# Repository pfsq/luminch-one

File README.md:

Luminch One
===========

Luminch One is an interactive lamp controlled by the movements of your hand.
Wave your hand over it to turn it on or off, or move your hand up or down
above it to change its brightness. Inside the lamp, an Arduino hooked to an
infrared distance sensor tracks your hand and sets the state and the
brightness of the LED lamp.

Copyright 2012 by [Francisco Castro](http://fran.cc)

EAGLE files, copyleft (ɔ) 2013 by [Pablo Fernández](http://theansweris27.wordpress.com)

[More info...](http://fran.cc/post/15139791161/luminch-one)

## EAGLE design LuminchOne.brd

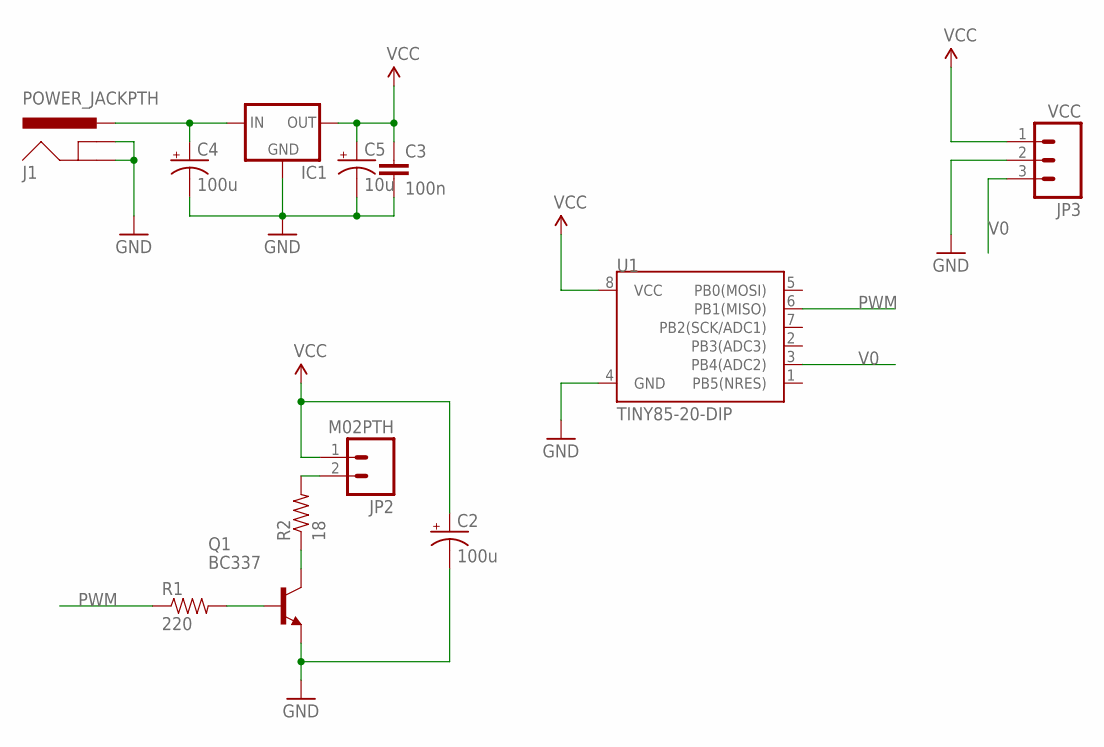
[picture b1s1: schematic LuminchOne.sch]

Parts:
C2, C4: 100u; CPOL-RADIAL-100UF-25V
C3: 100n; CAP-PTH-SMALL
C5: 10u; CPOL-RADIAL-10UF-25V
IC1: V_REG_78XX-TO-220; TO-220-ALT
J1: POWER_JACKPTH; POWER_JACK_PTH
JP2: M02PTH; 1X02
JP3: VCC; 1X03
Q1: BC337; TO92
R1: 220; AXIAL-0.4
R2: 18; AXIAL-0.6
U1: TINY85-20-DIP; DIP08

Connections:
GND: C2.2 (-), C3.2, C4.2 (-), C5.2 (-), IC1.GND, J1.GND, J1.GNDBREAK, JP3.2, Q1.1 (E), U1.4 (GND)
unnamed: Q1.2 (B), R1.P$2 (2)
unnamed: JP2.2, R2.P$2 (2)
unnamed: C4.1 (+), IC1.IN, J1.PWR
unnamed: Q1.3 (C), R2.P$1 (1)
PWM: R1.P$1 (1), U1.6 (PB1(MISO))
V0: JP3.3, U1.3 (PB4(ADC2))
VCC: C2.1 (+), C3.1, C5.1 (+), IC1.OUT, JP2.1, JP3.1, U1.8 (VCC)

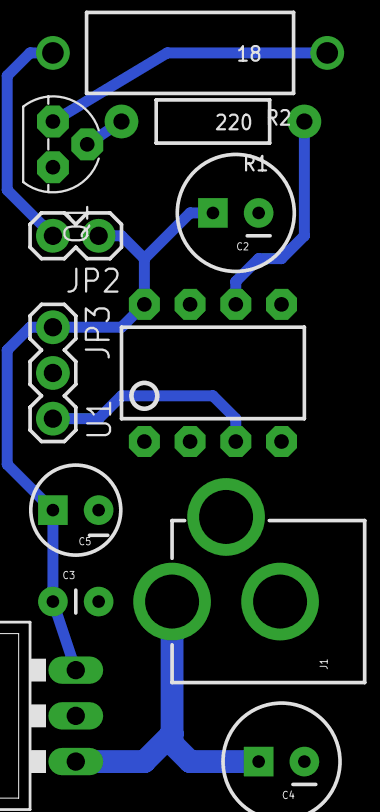
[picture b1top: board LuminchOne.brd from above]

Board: 2 copper layers, 12 parts (0 on the bottom side), 8 nets.

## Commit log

2013-10-05 Deletion
    Files not needed for the ATtiny85 project
2013-10-05 EAGLE Files
2013-10-08 update luminch-one.ino
    New pin definitions for ATtiny 85

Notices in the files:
parts and their libraries:
SparkFun-DigitalIC: Licensing: CC v3.0 Share-Alike You are welcome to use this library for commercial purposes.
